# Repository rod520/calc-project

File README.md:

# Pico Calc electronics design
### the electronics portion of an rpi Pico based calculator
## BOM:
| Part name | notes | Qty | Link |
| --- | --- | --- | --- |
| 3.2inch SPI Module ILI9341 SKU:MSP3217 | 3218 will also work as touchscreen is not wired | 1 | https://www.amazon.com/Pasuihcay-240X320-ILI9341-Occupies-MSP3218/dp/B0D5YFC594 |
| 6mm tactile switch |  | 36 | https://www.amazon.com/QTEATAK-Momentary-Tactile-Button-Switch/dp/B07VSNN9S2/ref=sxin_19_pa_sp_search_thematic_sspa?content-id=amzn1.sym.0c718b35-8c59-4938-97bf-b9d1819ea929%3Aamzn1.sym.0c718b35-8c59-4938-97bf-b9d1819ea929&crid=1LEC4S1U00IQO&cv_ct_cx=6mm+switch&keywords=6mm+switch&pd_rd_i=B07VSNN9S2&pd_rd_r=21af0360-bd6d-4493-9a72-96fcb04169b4&pd_rd_w=PqWIq&pd_rd_wg=IrpTp&pf_rd_p=0c718b35-8c59-4938-97bf-b9d1819ea929&pf_rd_r=WY0E907K72MT9R1R7JBZ&qid=1782495894&sbo=RZvfv%2F%2FHxDF%2BO5021pAnSA%3D%3D&sprefix=6mm+switch%2Caps%2C281&sr=1-1-e169343e-09af-4d41-85b1-8335fe8f32d0-spons&aref=jFNKZsthcz&sp_csd=d2lkZ2V0TmFtZT1zcF9zZWFyY2hfdGhlbWF0aWM&psc=1 |
| Pimoroni lipo pico | Note: pico 2 lipo will also work | 1 | https://vilros.com/products/pimoroni-pico-lipo-16mb |
| Lithium Ion Battery - 3.7V 2000mAh | Note: any battery with/connected to a JST-PH connector will work | 1 | https://www.adafruit.com/product/2011 |
| short plug male header | for pico, normal sized header pins and socket will work as well | 2 | https://www.adafruit.com/product/5584 |
| Short Socket Headers | see above | 2 | https://www.adafruit.com/product/5585 |

## design:
The pcb consists of two separated sections, the button matrix and the display connection, connected to an rpi with headers through 2 through hole pin connectors. Buttons are 6mm through hole, display is an MSP321**7** (no touch screen), connector is 1x20 2.54mm. 
**IMPORTANT:** the male header pins should be pointed down for access to bootsel, and the pico's usb port should be pointed outside, to the right if viewed from above.
## software:
see [zig-calc](https://github.com/rod520/zig-calc) for software, and also button overlay.

## WHY?
I wanted to make a clone of the numworks calculator, but I realized that wasnt feasible and cheap, so I eventually landed on making a pi-hat like extension for an rpi pico. The pico clone Pimoroni LiPo Pico can connect to  an optional Lithium Ion Battery, so this calculator will (eventually) have nearly every feature of the numworks, albeit with a vertical display, thicker case, and cheap clicky buttons. 

## materials:
1. 36 6mm through hole tactile buttons
2. 2 1x20 female/socket connectors, **2.54 mm**, I'm planning on using Adafruit's short socket headers
3. 2 matching 1x20 male/pin connectors, **2.54 mm**, I'm planning on using Adafruit's short pin headers, or you can stick with the pico's default
4. MSP3217 or MSP3218, both work, but you will not be able to use the MSP3218's touchscreen
5. soldering materials
6. an rpi pico, with headers facing down, (OPTIONAL) pimoroni lipo pico in case you want to use a rechargeable battery
7. (OPTIONAL) a JST-PH battery for the pimoroni lipo pico

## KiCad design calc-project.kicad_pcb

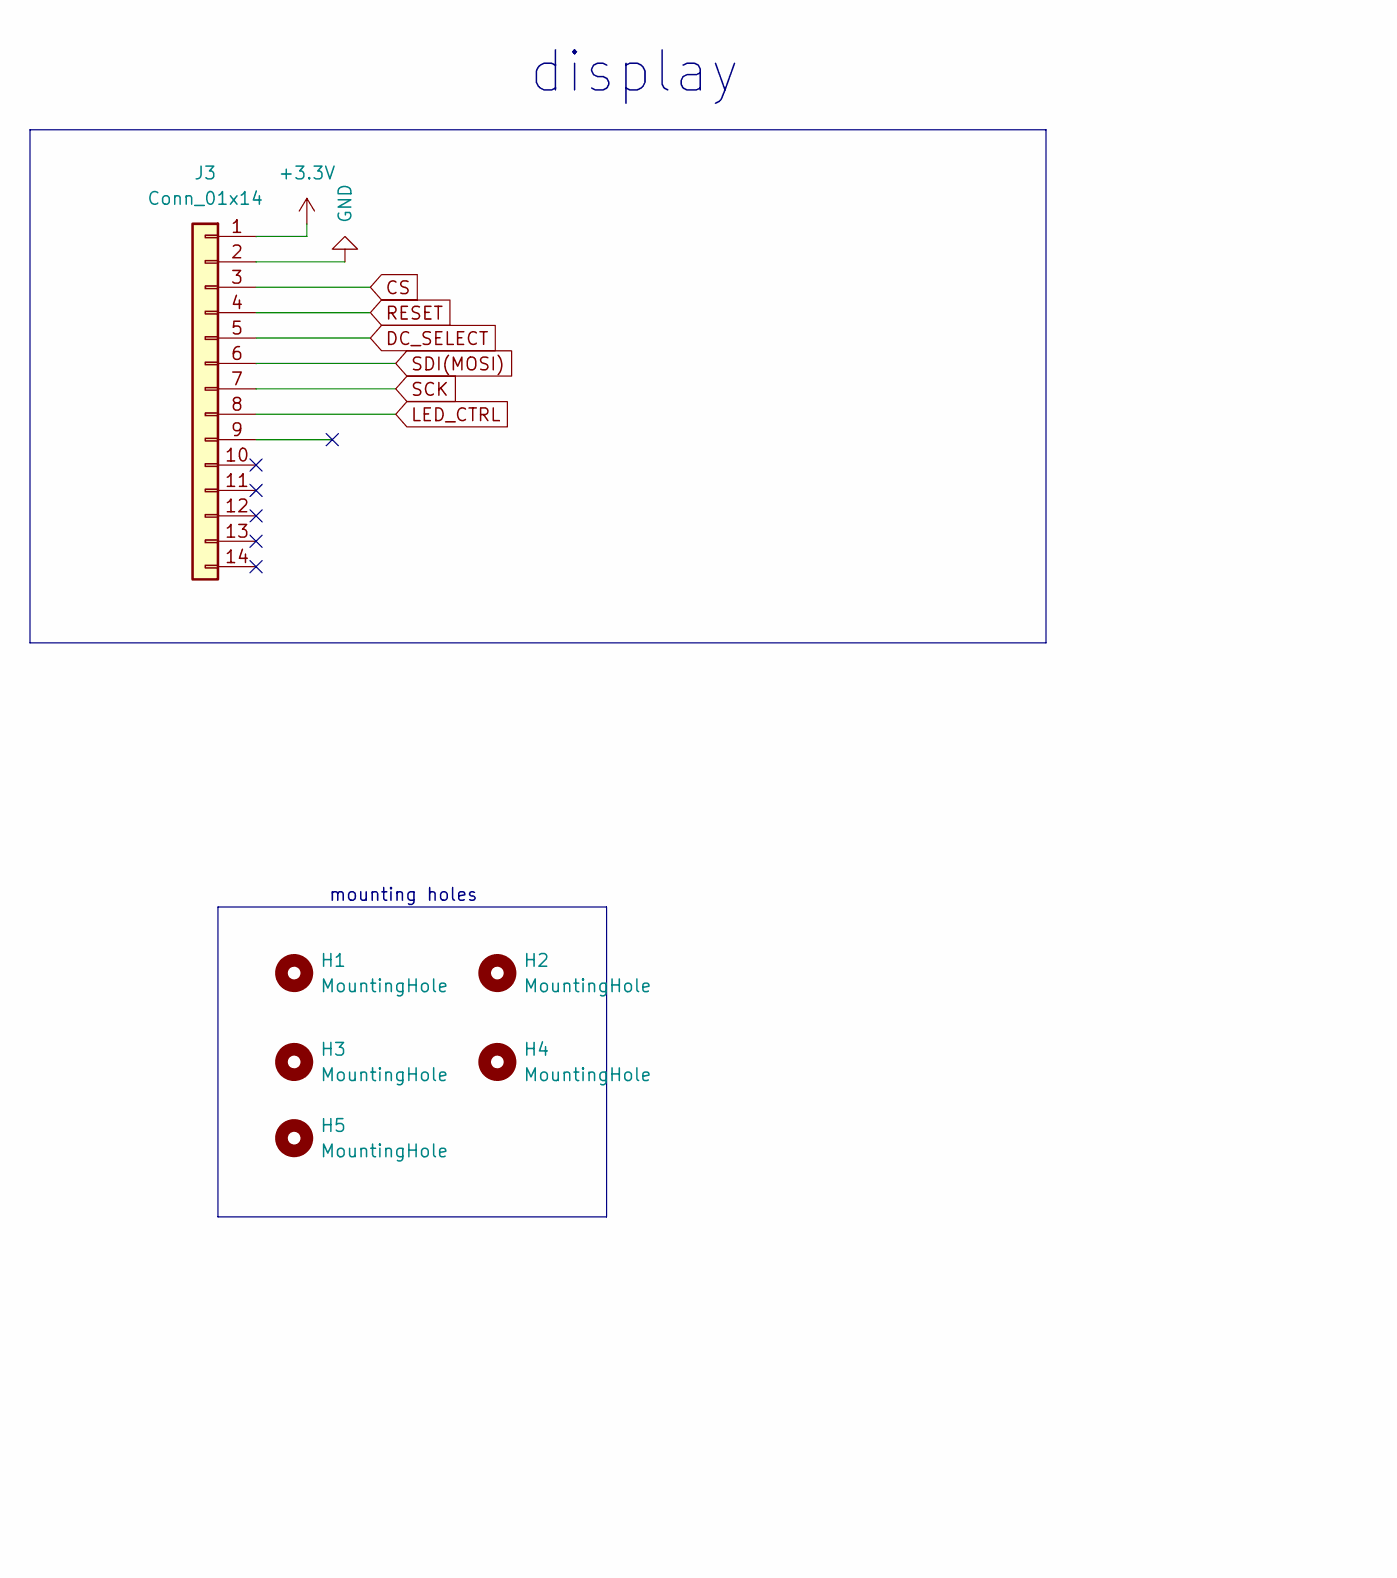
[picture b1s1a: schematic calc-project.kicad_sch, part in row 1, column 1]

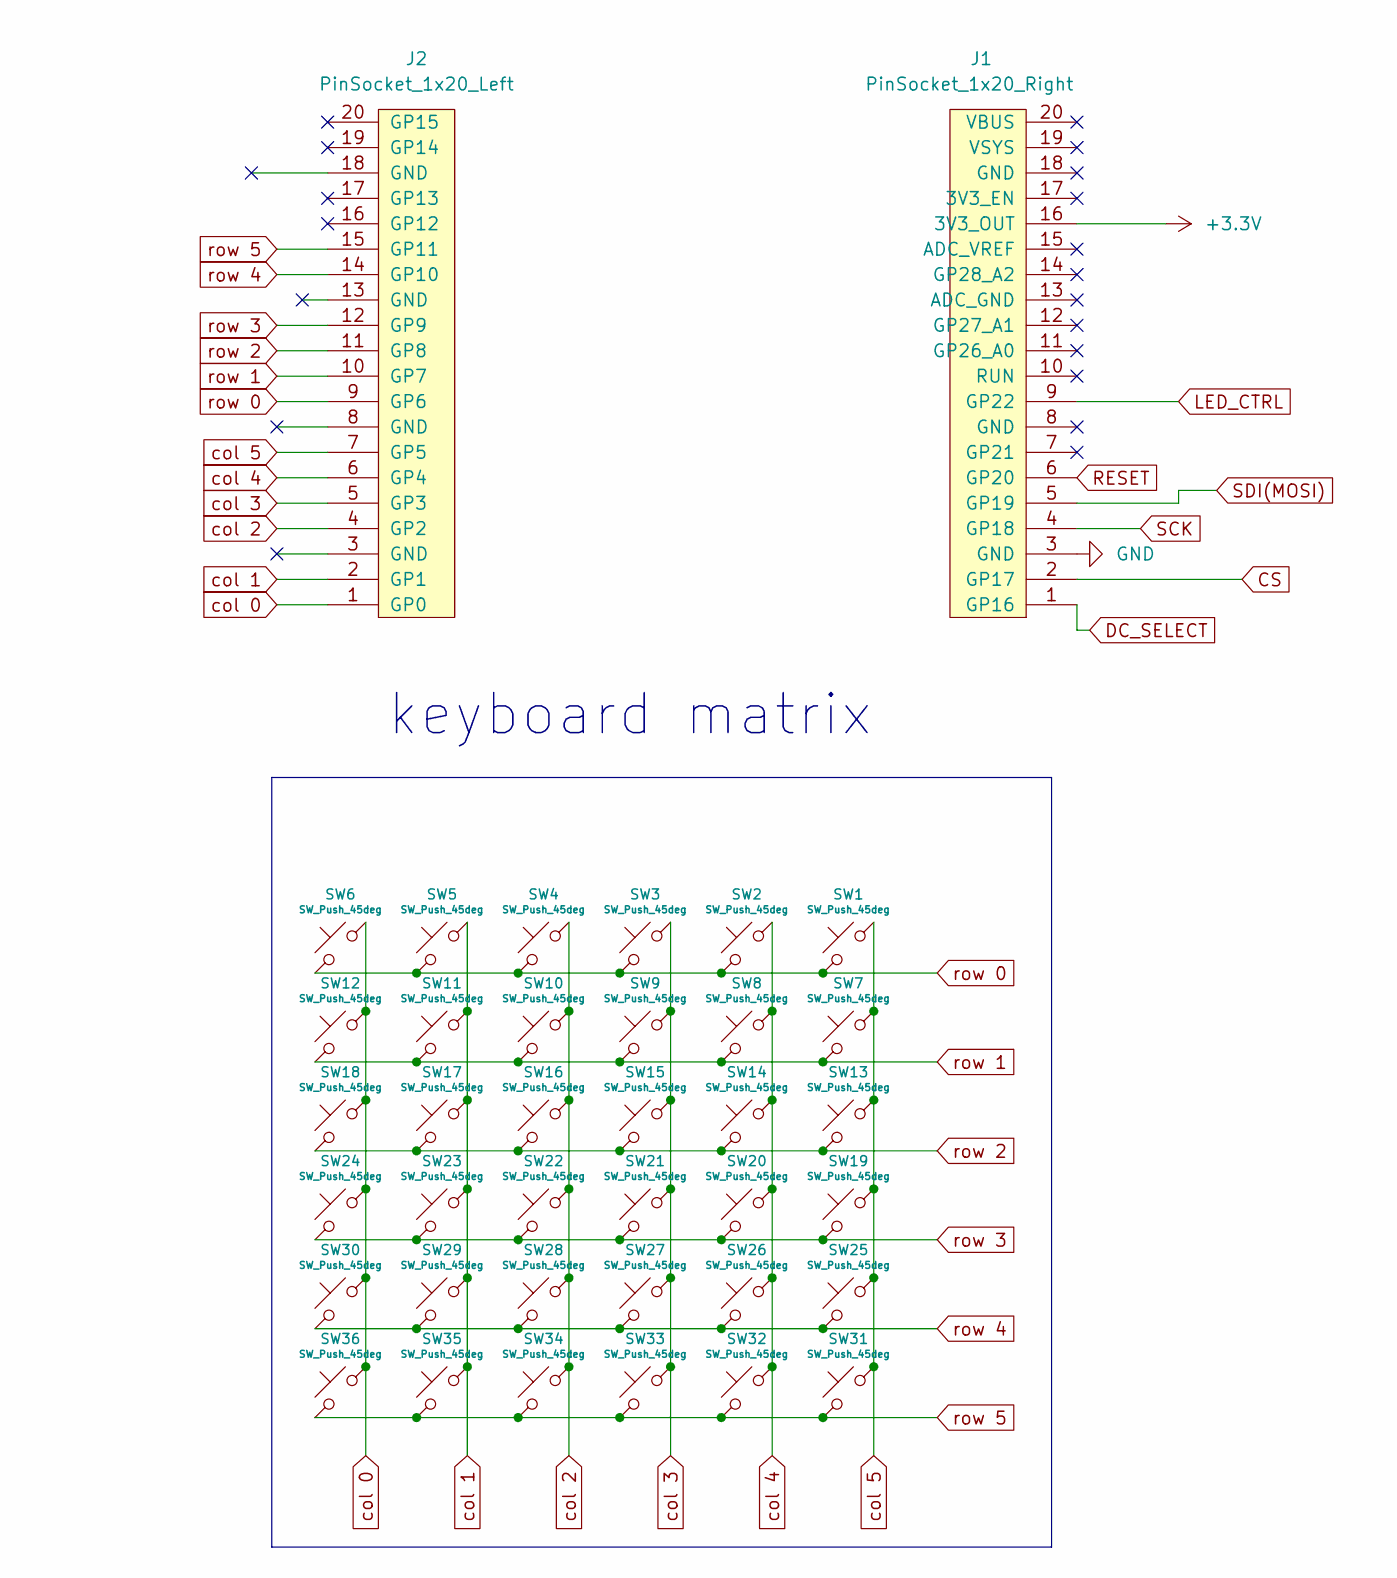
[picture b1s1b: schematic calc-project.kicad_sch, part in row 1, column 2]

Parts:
H1, H2, H3, H4, H5: MountingHole; MountingHole_2.1mm
J1: PinSocket_1x20_Right; PinSocket_1x20_P2.54mm_Vertical
J2: PinSocket_1x20_Left; PinSocket_1x20_P2.54mm_Vertical
J3: Conn_01x14; castel_toScreen
SW1, SW2, SW3, SW4, SW5, SW6, SW7, SW8, SW9, SW10, SW11, SW12, SW13, SW14, SW15, SW16, SW17, SW18, SW19, SW20, SW21, SW22, SW23, SW24, SW25, SW26, SW27, SW28, SW29, SW30, SW31, SW32, SW33, SW34, SW35, SW36: SW_Push_45deg; SW_PUSH_6mm_centered

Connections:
+3.3V: J1.16 (3V3_OUT), J3.1
CS: J1.2 (GP17), J3.3
DC_SELECT: J1.1 (GP16), J3.5
GND: J1.3 (GND), J3.2
LED_CTRL: J1.9 (GP22), J3.8
RESET: J1.6 (GP20), J3.4
SCK: J1.4 (GP18), J3.7
SDI(MOSI): J1.5 (GP19), J3.6
col 0: J2.1 (GP0), SW6.1, SW12.1, SW18.1, SW24.1, SW30.1, SW36.1
col 1: J2.2 (GP1), SW5.1, SW11.1, SW17.1, SW23.1, SW29.1, SW35.1
col 2: J2.4 (GP2), SW4.1, SW10.1, SW16.1, SW22.1, SW28.1, SW34.1
col 3: J2.5 (GP3), SW3.1, SW9.1, SW15.1, SW21.1, SW27.1, SW33.1
col 4: J2.6 (GP4), SW2.1, SW8.1, SW14.1, SW20.1, SW26.1, SW32.1
col 5: J2.7 (GP5), SW1.1, SW7.1, SW13.1, SW19.1, SW25.1, SW31.1
row 0: J2.9 (GP6), SW1.2, SW2.2, SW3.2, SW4.2, SW5.2, SW6.2
row 1: J2.10 (GP7), SW7.2, SW8.2, SW9.2, SW10.2, SW11.2, SW12.2
row 2: J2.11 (GP8), SW13.2, SW14.2, SW15.2, SW16.2, SW17.2, SW18.2
row 3: J2.12 (GP9), SW19.2, SW20.2, SW21.2, SW22.2, SW23.2, SW24.2
row 4: J2.14 (GP10), SW25.2, SW26.2, SW27.2, SW28.2, SW29.2, SW30.2
row 5: J2.15 (GP11), SW31.2, SW32.2, SW33.2, SW34.2, SW35.2, SW36.2

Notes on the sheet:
display
keyboard matrix
mounting holes

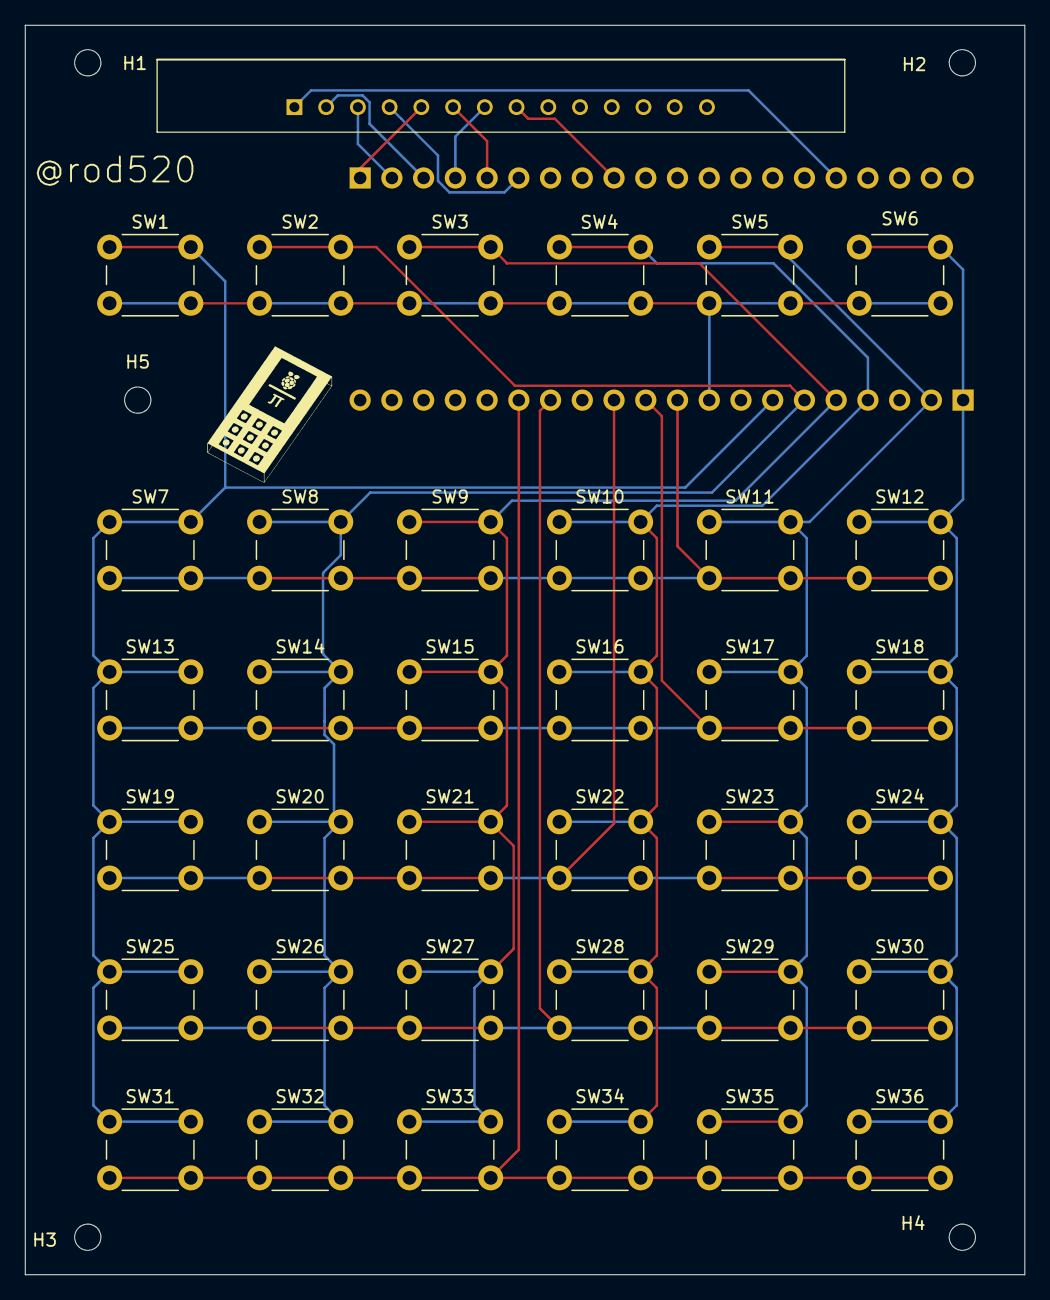
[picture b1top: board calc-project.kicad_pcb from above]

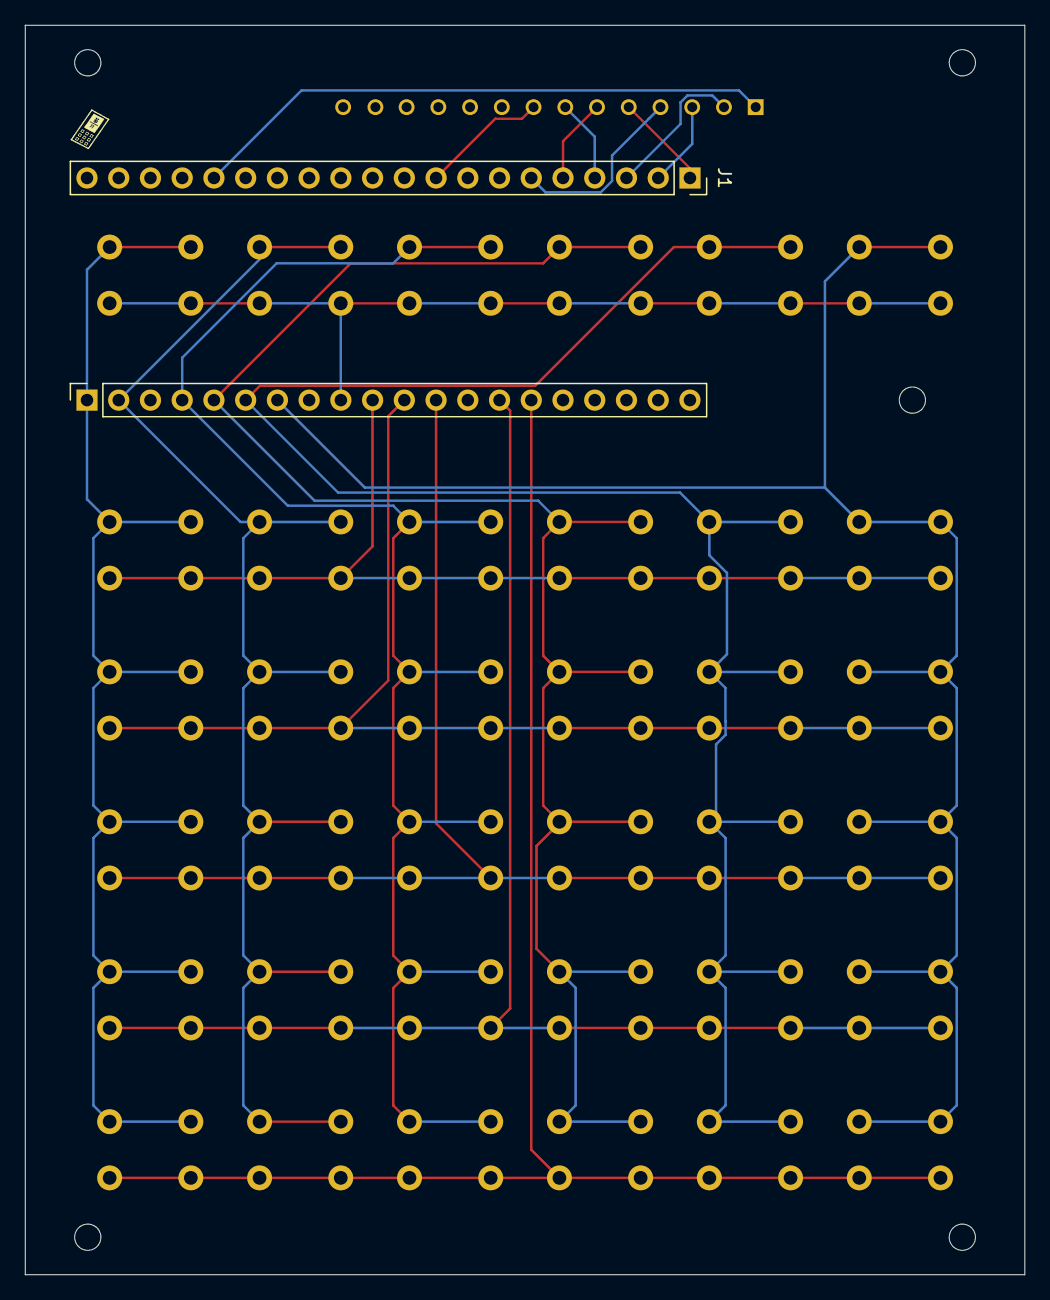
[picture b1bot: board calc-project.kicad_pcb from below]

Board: 2 copper layers, 80.0 x 100.0 mm, 44 parts (2 on the bottom side), 20 nets.

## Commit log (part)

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2026-06-04 added rpi pico, took away connectors, idk what else
    idk what i did
2026-06-05 change gitignore, other thing
2026-06-05 idek if this is progress or not
2026-06-09 we're now setting ourselves up for new screen, still need alignment
2026-06-09 fixed names, seems like schematic is good
2026-06-16 edited some stuff
    fixed footprint, wired up, moved screen
2026-06-22 routing
    routing
2026-06-22 capabilities
    yeah
    did use kicad happy just to check and make sure we had capabilities
2026-06-22 wrong pin
2026-06-23 random stuff, i think it helps
2026-06-23 better dimensions
    Didn't have to be so wide, so I put all the components closer together and rerouted the whole thing
2026-06-24 one last change
2026-06-25 created gerbers, added logo
2026-06-25 create readme
    yeah
2026-06-25 idek what just happened
    but im trusting its fine
2026-06-25 Delete 3dComponents/FH12S-40S-0.5SH(55)_CL0586-0640-0-55_3DDrawing_STEP_0001219161S(connector) directory
    whoops wasn't actually supposed to leave that there
2026-06-25 Delete 3dComponents/TL3315NF160Q(switch) directory
    this is the wrong switch anyway
2026-06-25 housecleaning
2026-06-26 replaced old headers, now new ones
    also took out routing for rows
2026-06-26 routing
2026-06-26 BOM
    bill of materials
2026-06-26 Revise README sections and update materials list
    Updated hardware section to mechanical and added details about materials.
